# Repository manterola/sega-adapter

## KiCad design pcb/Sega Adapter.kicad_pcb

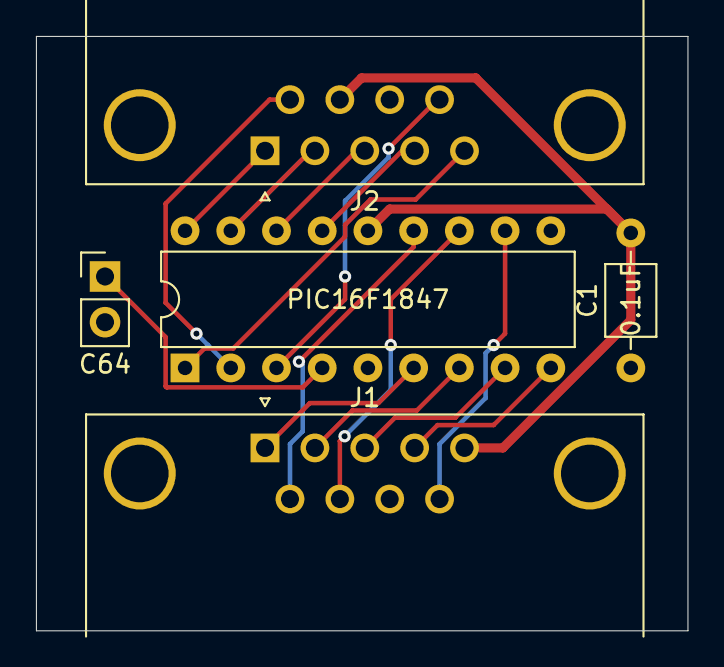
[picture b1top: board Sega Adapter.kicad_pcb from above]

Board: 2 copper layers, 36.2 x 33.0 mm, 5 parts (0 on the bottom side), 17 nets.

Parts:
C1: 0.1uF; C_Axial_L3.8mm_D2.6mm_P7.50mm_Horizontal
J1: Sega; DSUB-9_Male_Horizontal_P2.77x2.84mm_EdgePinOffset7.70mm_Hou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
J2: Atari; DSUB-9_Female_Horizontal_P2.77x2.84mm_EdgePinOffset7.70mm_H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
JP1: C64; PinHeader_1x02_P2.54mm_Vertical
U1: PIC16F1847; DIP-18_W7.62mm

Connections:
+5V: C1.2, J1.5, J2.7, U1.14
GND: C1.1, J1.0, J1.8, J2.0, J2.8, JP1.2, U1.5
unnamed: J1.1, U1.6
unnamed: J1.2, U1.7
unnamed: J1.3, U1.8
unnamed: J1.4, U1.9
unnamed: J1.6, U1.13
unnamed: J1.7, U1.12
unnamed: J1.9, U1.11
unnamed: J2.1, U1.18
unnamed: J2.2, U1.17
unnamed: J2.3, U1.16
unnamed: J2.4, U1.15
unnamed: J2.5, U1.1
unnamed: J2.6, U1.2
unnamed: J2.9, U1.3
unnamed: JP1.1, U1.4

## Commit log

2021-03-10 Add KiCad files
2021-03-14 Finished schematic
2021-03-15 More compact PCB
